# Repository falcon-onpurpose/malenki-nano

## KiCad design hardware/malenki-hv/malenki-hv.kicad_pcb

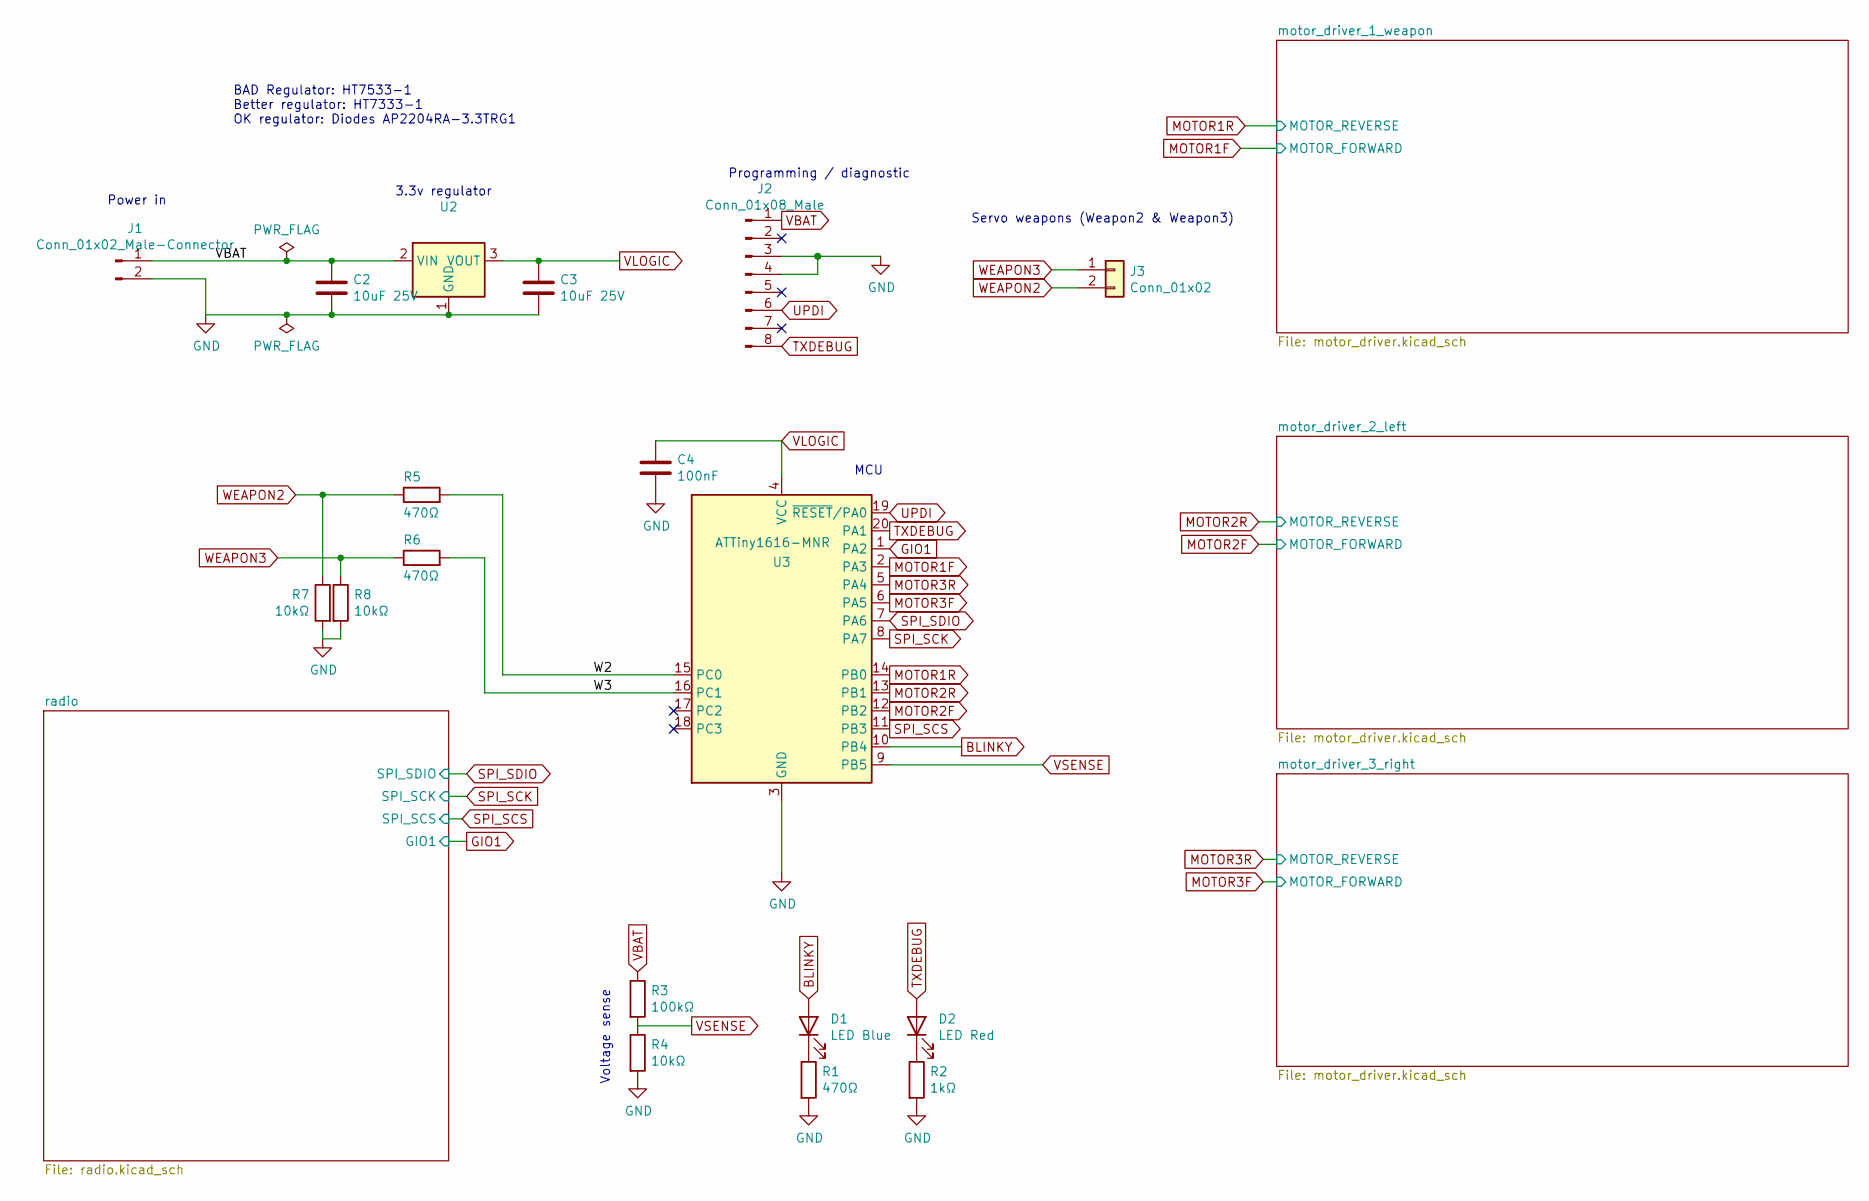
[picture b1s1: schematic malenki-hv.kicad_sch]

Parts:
C2, C3: 10uF 25V; C_0603_1608Metric; MPN CL10A106MA8NRNC; LCSC C96446
C4: 100nF; C_0402_1005Metric; MPN CL05B104KB54PNC; LCSC C307331
D1: LED Blue; LED_0603_1608Metric; MPN 19-217/BHC-ZL1M2RY/3T; LCSC C72041
D2: LED Red; LED_0603_1608Metric; MPN KT-0603R; LCSC C2286
J1: Conn_01x02_Male-Connector; malenkipower
J2: Conn_01x08_Male; SOIC_clipProgSmall
J3: Conn_01x02; wirepad_2
R1, R5, R6: 470Ω; R_0402_1005Metric; MPN 0402WGF4700TCE; LCSC C25117
R2: 1kΩ; R_0402_1005Metric; MPN 0402WGF1001TCE; LCSC C11702
R3: 100kΩ; R_0402_1005Metric; MPN 0402WGF1003TCE; LCSC C25741
R4, R7, R8: 10kΩ; R_0402_1005Metric; MPN 0402WGF1002TCE; LCSC C25744
U2: 300mA Fixed 3.3V Positive 24V SOT-89 Voltage Regu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; SOT-89-3; MPN HT7333-1-MS; LCSC C7434186
U3: ATTiny1616-MNR; VQFN-20-1EP_3x3mm_P0.4mm_EP1.7x1.7mm; MPN ATTINY1616-MNR; LCSC C507118

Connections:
/W2: R5.2, U3.15 (PC0)
/W3: R6.2, U3.16 (PC1)
BLINKY: D1.2 (A), U3.10 (PB4)
GIO1: U3.1 (PA2); also elsewhere on the board
GND: C2.2, C3.2, C4.2, J1.2, J2.3, J2.4, R1.2, R2.2, R4.2, R7.2, R8.2, U2.1 (GND), U3.3 (GND), U3.21 (GND); also elsewhere on the board
MOTOR1F: U3.2 (PA3); also elsewhere on the board
MOTOR1R: U3.14 (PB0); also elsewhere on the board
MOTOR2F: U3.12 (PB2); also elsewhere on the board
MOTOR2R: U3.13 (PB1); also elsewhere on the board
MOTOR3F: U3.6 (PA5); also elsewhere on the board
MOTOR3R: U3.5 (PA4); also elsewhere on the board
unnamed: D1.1 (K), R1.1
unnamed: D2.1 (K), R2.1
SPI_SCK: U3.8 (PA7); also elsewhere on the board
SPI_SCS: U3.11 (PB3); also elsewhere on the board
SPI_SDIO: U3.7 (PA6); also elsewhere on the board
TXDEBUG: D2.2 (A), J2.8, U3.20 (PA1)
UPDI: J2.6, U3.19 (~RESET/PA0)
VBAT: C2.1, J1.1, J2.1, R3.1, U2.2 (VIN); also elsewhere on the board
VLOGIC: C3.1, C4.1, U2.3 (VOUT), U3.4 (VCC); also elsewhere on the board
VSENSE: R3.2, R4.1, U3.9 (PB5)
WEAPON2: J3.2, R5.1, R7.1
WEAPON3: J3.1, R6.1, R8.1

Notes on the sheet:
Voltage sense
Power in
Servo weapons (Weapon2 & Weapon3)
Programming / diagnostic
BAD Regulator: HT7533-1 Better regulator: HT7333-1 OK regulator: Diodes AP2204RA-3.3TRG1
MCU
3.3v regulator

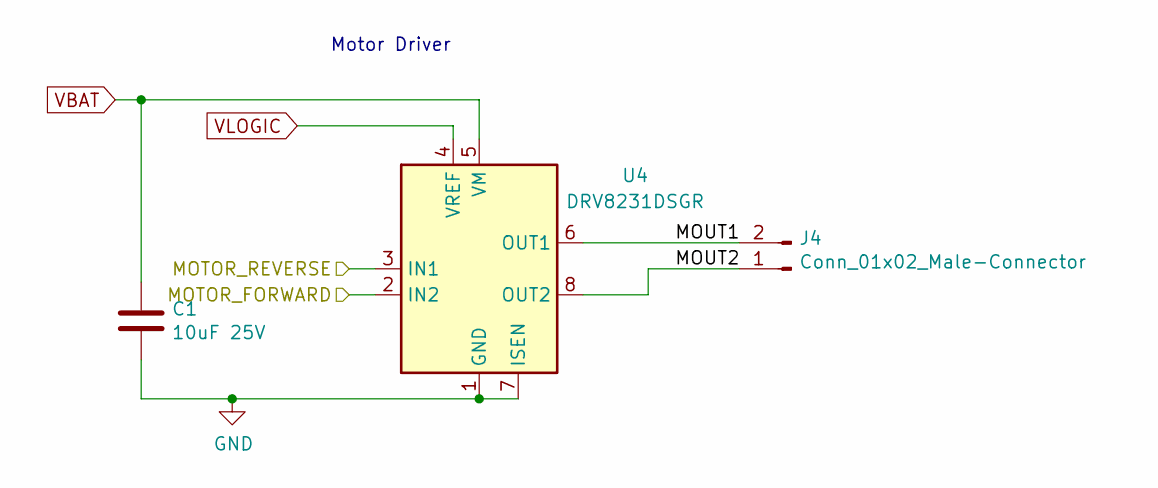
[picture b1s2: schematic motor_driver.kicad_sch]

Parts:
C1: 10uF 25V; C_0603_1608Metric; MPN CL10A106MA8NRNC; LCSC C96446
J4: Conn_01x02_Male-Connector; PinHeader_1x02_P2.54mm_BIG1
U4: DRV8231DSGR; WSON-8-1EP_2x2mm_P0.5mm_EP0.9x1.6mm; MPN DRV8231DSGR; LCSC C3681197

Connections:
/motor_driver_1_weapon/MOUT1: J4.2, U4.6 (OUT1)
/motor_driver_1_weapon/MOUT2: J4.1, U4.8 (OUT2)
GND: C1.2, U4.1 (GND), U4.7 (ISEN), U4.9 (GND); also elsewhere on the board
MOTOR1F: U4.2 (IN2); also elsewhere on the board
MOTOR1R: U4.3 (IN1); also elsewhere on the board
VBAT: C1.1, U4.5 (VM); also elsewhere on the board
VLOGIC: U4.4 (VREF); also elsewhere on the board

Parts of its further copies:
C5, C6: 10uF 25V; C_0603_1608Metric; MPN CL10A106MA8NRNC; LCSC C96446
J5, J6: Conn_01x02_Male-Connector; PinHeader_1x02_P2.54mm_BIG1
U5, U6: DRV8231DSGR; WSON-8-1EP_2x2mm_P0.5mm_EP0.9x1.6mm; MPN DRV8231DSGR; LCSC C3681197

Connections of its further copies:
/motor_driver_2_left/MOUT1: J5.2, U5.6 (OUT1)
/motor_driver_2_left/MOUT2: J5.1, U5.8 (OUT2)
/motor_driver_3_right/MOUT1: J6.2, U6.6 (OUT1)
/motor_driver_3_right/MOUT2: J6.1, U6.8 (OUT2)
GND: C5.2, C6.2, U5.1 (GND), U5.7 (ISEN), U5.9 (GND), U6.1 (GND), U6.7 (ISEN), U6.9 (GND); also elsewhere on the board
MOTOR2F: U5.2 (IN2); also elsewhere on the board
MOTOR2R: U5.3 (IN1); also elsewhere on the board
MOTOR3F: U6.2 (IN2); also elsewhere on the board
MOTOR3R: U6.3 (IN1); also elsewhere on the board
VBAT: C5.1, C6.1, U5.5 (VM), U6.5 (VM); also elsewhere on the board
VLOGIC: U5.4 (VREF), U6.4 (VREF); also elsewhere on the board

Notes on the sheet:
Motor Driver

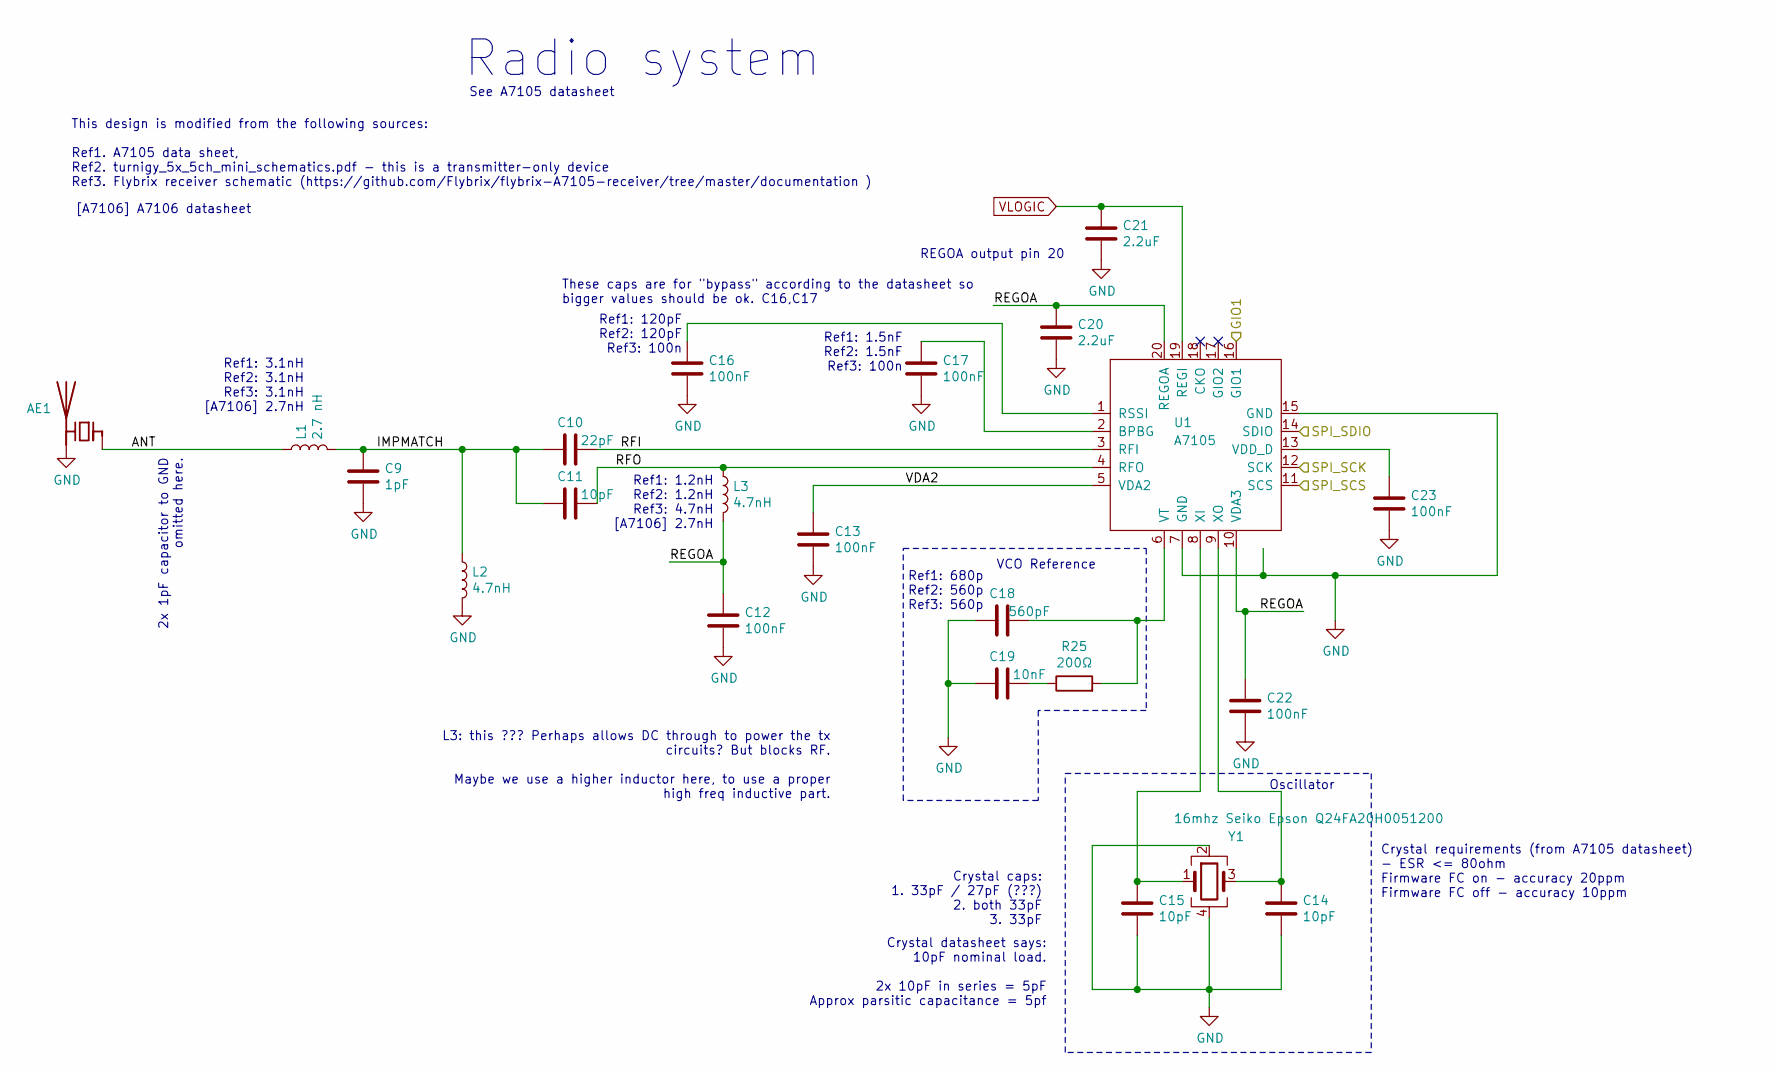
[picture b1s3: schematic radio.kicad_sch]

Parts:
AE1: malenki_antenna
C9: 1pF; C_0402_1005Metric; MPN 0402CG1R0C500NT; LCSC C1550
C10: 22pF; C_0402_1005Metric; MPN 0402CG220J500NT; LCSC C1555
C11, C14, C15: 10pF; C_0402_1005Metric; MPN CL05C100JB5NNNC; LCSC C32949
C12, C13, C16, C17, C22, C23: 100nF; C_0402_1005Metric; MPN CL05B104KB54PNC; LCSC C307331
C18: 560pF; C_0402_1005Metric; MPN 0402B561K500NT; LCSC C1539
C19: 10nF; C_0402_1005Metric; MPN CL05B103KB5NNNC; LCSC C15195
C20, C21: 2.2uF; C_0603_1608Metric; MPN CL10A225KO8NNNC; LCSC C23630
L1: 2.7 nH; L_0402_1005Metric; MPN MLK1005S2N7ST000; LCSC C76791
L2, L3: 4.7nH; L_0402_1005Metric; MPN LQW15AN4N7D10D; LCSC C341688
R25: 200Ω; R_0402_1005Metric; MPN 0402WGF2000TCE; LCSC C25087
U1: A7105; a7105-QFN-20; MPN A71X05AQFI/Q; LCSC C126376
Y1: 16mhz Seiko Epson Q24FA20H0051200; Crystal_SMD_2520-4Pin_2.5x2.0mm; MPN Q24FA20H00512; LCSC C255947

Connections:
/radio/ANT: AE1.1 (FEED), L1.1
/radio/IMPMATCH: C9.1, C10.1, C11.1, L1.2, L2.1
/radio/REGOA: C12.1, C20.1, C22.1, L3.2, U1.10 (VDA3), U1.20 (REGOA)
/radio/RFI: C10.2, U1.3 (RFI)
/radio/RFO: C11.2, L3.1, U1.4 (RFO)
/radio/VDA2: C13.1, U1.5 (VDA2)
GIO1: U1.16 (GIO1); also elsewhere on the board
GND: AE1.2 (PCB_Trace), C9.2, C12.2, C13.2, C14.2, C15.2, C16.2, C17.2, C18.1, C19.2, C20.2, C21.2, C22.2, C23.2, L2.2, U1.7 (GND), U1.15 (GND), U1.21 (GND), Y1.2, Y1.4; also elsewhere on the board
unnamed: C19.1, R25.1
unnamed: C17.1, U1.2 (BPBG)
unnamed: C16.1, U1.1 (RSSI)
unnamed: C23.1, U1.13 (VDD_D)
unnamed: C18.2, R25.2, U1.6 (VT)
unnamed: C15.1, U1.8 (XI), Y1.1
unnamed: C14.1, U1.9 (XO), Y1.3
SPI_SCK: U1.12 (SCK); also elsewhere on the board
SPI_SCS: U1.11 (SCS); also elsewhere on the board
SPI_SDIO: U1.14 (SDIO); also elsewhere on the board
VLOGIC: C21.1, U1.19 (REGI); also elsewhere on the board

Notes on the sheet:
REGOA output pin 20
Radio system
Ref1: 3.1nH Ref2: 3.1nH Ref3: 3.1nH [A7106] 2.7nH
See A7105 datasheet
Ref1: 120pF Ref2: 120pF Ref3: 100n
Crystal datasheet says: 10pF nominal load. 2x 10pF in series = 5pF Approx parsitic capacitance = 5pf
Oscillator
Ref1: 1.2nH Ref2: 1.2nH Ref3: 4.7nH [A7106] 2.7nH
L3: this ??? Perhaps allows DC through to power the tx circuits? But blocks RF. Maybe we use a higher inductor here, to use a proper high freq inductive part.
Crystal requirements (from A7105 datasheet) - ESR <= 80ohm Firmware FC on - accuracy 20ppm Firmware FC off - accuracy 10ppm
[A7106] A7106 datasheet
These caps are for "bypass" according to the datasheet so bigger values should be ok. C16,C17
Ref1: 680p Ref2: 560p Ref3: 560p
VCO Reference
2x 1pF capacitor to GND omitted here.
This design is modified from the following sources: Ref1. A7105 data sheet, Ref2. turnigy_5x_5ch_mini_schematics.pdf - this is a transmitter-only device Ref3. Flybrix receiver schematic (https://github.com/Flybrix/flybrix-A7105-receiver/tree/master/documentation )
Crystal caps: 1. 33pF / 27pF (???) 2. both 33pF 3. 33pF
Ref1: 1.5nF Ref2: 1.5nF Ref3: 100n

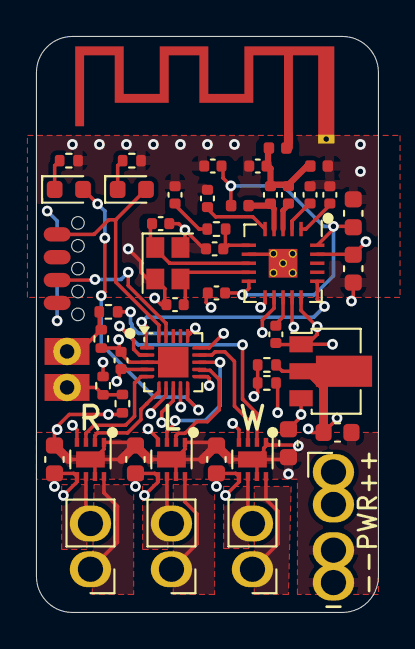
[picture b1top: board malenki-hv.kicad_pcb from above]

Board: 4 copper layers, 19.0 x 32.0 mm, 49 parts (1 on the bottom side), 42 nets.

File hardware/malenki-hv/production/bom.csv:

Designator,Footprint,Quantity,Value,LCSC Part #
"C1, C2, C3, C5, C6",0603,5,10uF 25V,C96446
C10,0402,1,22pF,C1555
"C11, C14, C15",0402,3,10pF,C32949
"C12, C13, C16, C17, C22, C23, C4",0402,7,100nF,C307331
C18,0402,1,560pF,C1539
C19,0402,1,10nF,C15195
"C20, C21",0603,2,2.2uF,C23630
C9,0402,1,1pF,C1550
D1,0603,1,LED Blue,C72041
D2,0603,1,LED Red,C2286
L1,0402,1,2.7 nH,C76791
"L2, L3",0402,2,4.7nH,C341688
"R1, R5, R6",0402,3,470Ω,C25117
R2,0402,1,1kΩ,C11702
R25,0402,1,200Ω,C25087
R3,0402,1,100kΩ,C25741
"R4, R7, R8",0402,3,10kΩ,C25744
U1,a7105-QFN-20,1,A7105,C126376
U2,SOT-89-3,1,"300mA Fixed 3.3V Positive 24V SOT-89 Voltage Regulators - Linear, Low Drop Out (LDO) Regulators",C7434186
U3,VQFN-20-1EP_3x3mm_P0.4mm_EP1.7x1.7mm,1,ATTiny1616-MNR,C507118
"U4, U5, U6",WSON-8-1EP_2x2mm_P0.5mm_EP0.9x1.6mm,3,DRV8231DSGR,C3681197
Y1,Crystal_SMD_2520-4Pin_2.5x2.0mm,1,16mhz Seiko Epson Q24FA20H0051200,C255947

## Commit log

2025-08-05 Updated u1 QFN symbol by adding solder paste layer, minor schematic updates to fix check errors, converted to kiCad 9, Updated BOM with LSCS numbers, fixed BOM errors.
2025-08-05 Removed old bom file, as new boms are automatically generated under a different name.
2025-08-05 New BOM file as automatically generated from kiCad 9.
2025-08-06 Add F.Paste layer to U1, A7105
2025-09-26 no message
